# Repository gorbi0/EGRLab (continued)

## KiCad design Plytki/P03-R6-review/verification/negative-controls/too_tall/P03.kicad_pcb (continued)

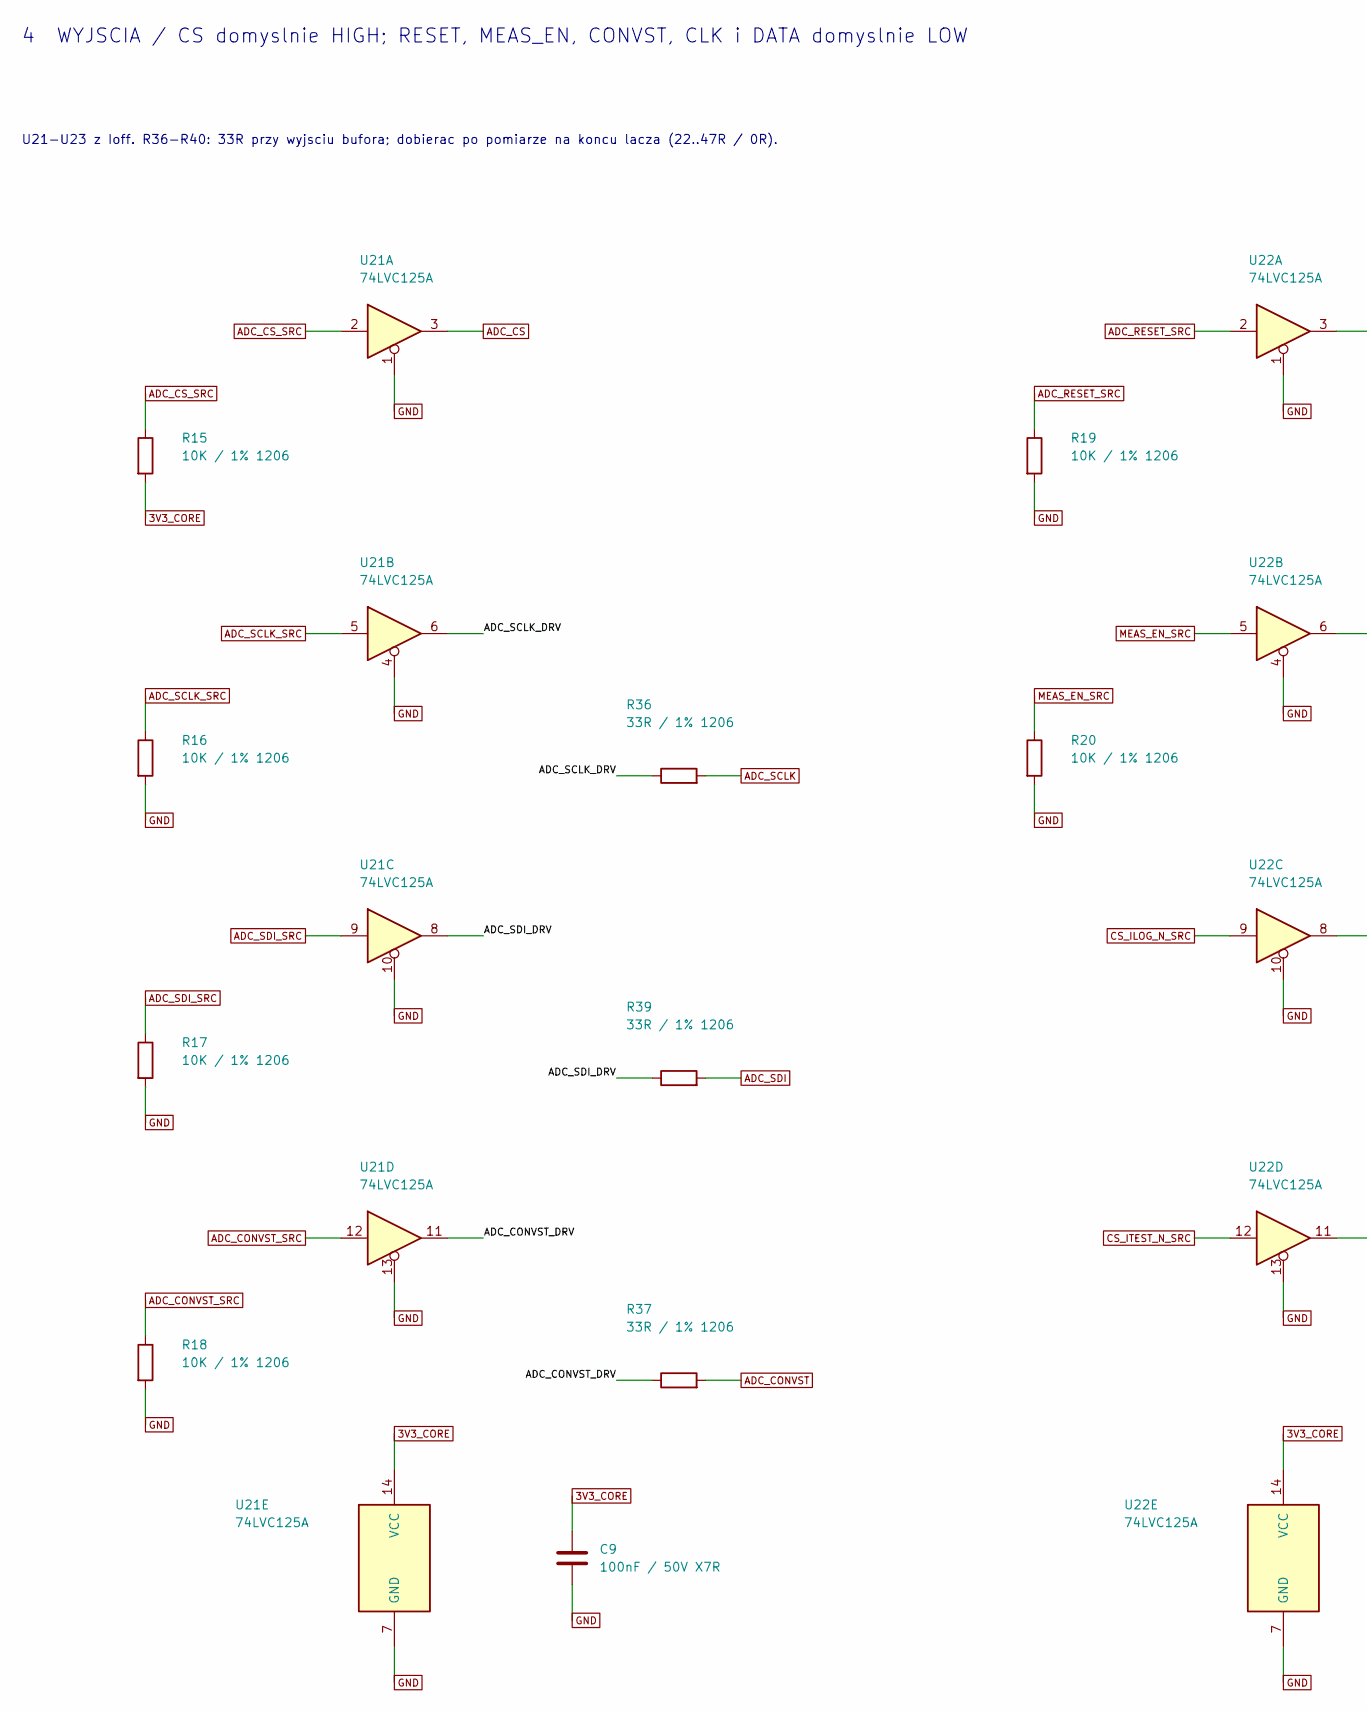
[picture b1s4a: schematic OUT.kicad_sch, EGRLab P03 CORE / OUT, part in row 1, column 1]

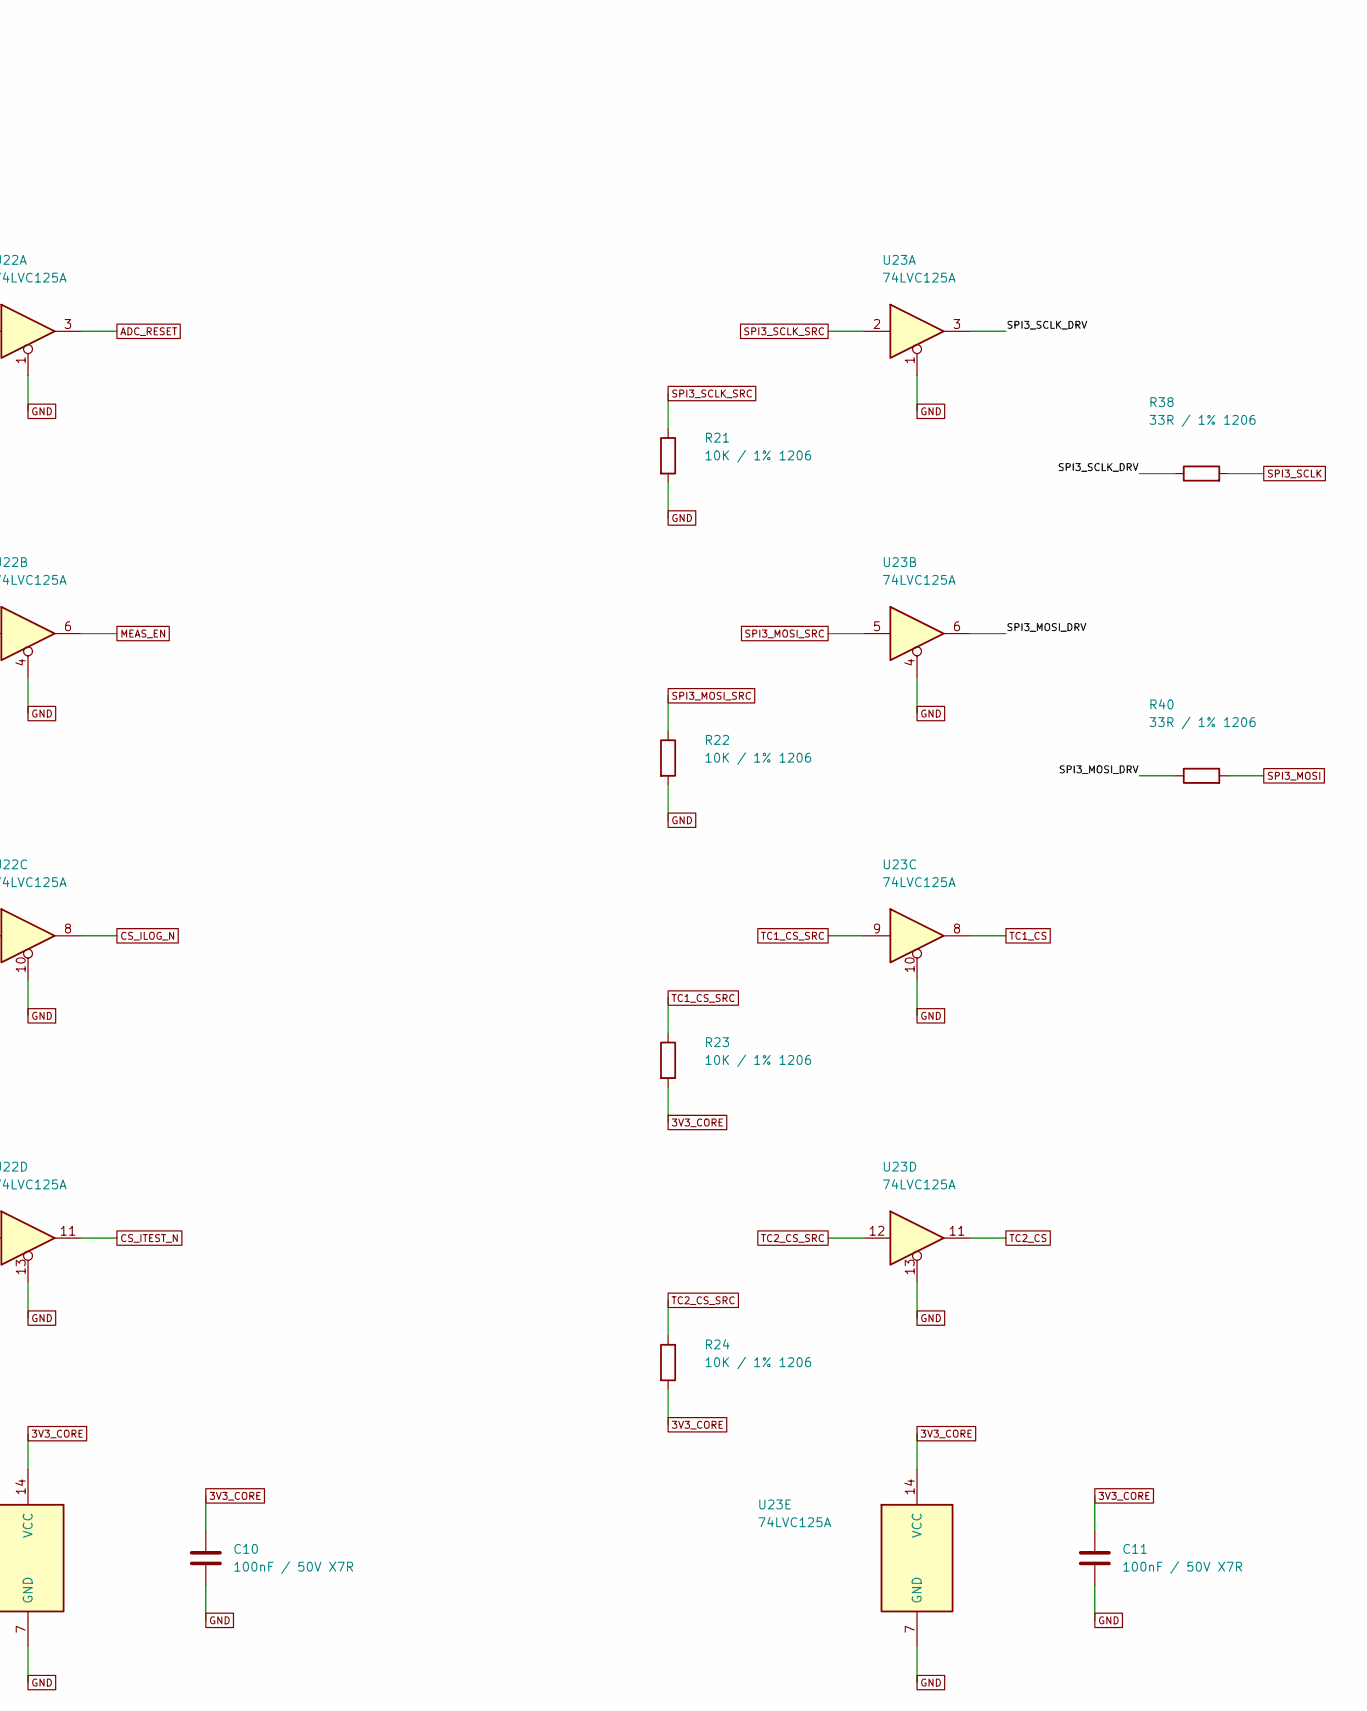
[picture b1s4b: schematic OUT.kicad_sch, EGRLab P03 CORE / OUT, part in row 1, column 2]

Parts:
C9, C10, C11: 100nF / 50V X7R; C_1206_3216Metric_Pad1.33x1.80mm_HandSolder; MPN GRM31CR71H104KA01L
R15, R16, R17, R18, R19, R20, R21, R22, R23, R24: 10K / 1% 1206; R_1206_3216Metric_Pad1.30x1.75mm_HandSolder; MPN RC1206FR-0710KL
R36, R37, R38, R39, R40: 33R / 1% 1206; R_1206_3216Metric_Pad1.30x1.75mm_HandSolder; MPN RC1206FR-0733RL
U21, U22, U23: 74LVC125A; SOIC-14_3.9x8.7mm_P1.27mm; MPN 74LVC125AD,118 (Nexperia)

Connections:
/OUT/ADC_CONVST_DRV: R37.1, U21.11
/OUT/ADC_SCLK_DRV: R36.1, U21.6
/OUT/ADC_SDI_DRV: R39.1, U21.8
/OUT/SPI3_MOSI_DRV: R40.1, U23.6
/OUT/SPI3_SCLK_DRV: R38.1, U23.3
ADC_CONVST: R37.2; also elsewhere on the board
ADC_CONVST_SRC: R18.1, U21.12; also elsewhere on the board
ADC_CS: U21.3; also elsewhere on the board
ADC_CS_SRC: R15.1, U21.2; also elsewhere on the board
ADC_RESET: U22.3; also elsewhere on the board
ADC_RESET_SRC: R19.1, U22.2; also elsewhere on the board
ADC_SCLK: R36.2; also elsewhere on the board
ADC_SCLK_SRC: R16.1, U21.5; also elsewhere on the board
ADC_SDI: R39.2; also elsewhere on the board
ADC_SDI_SRC: R17.1, U21.9; also elsewhere on the board
CS_ILOG_N_SRC: U22.9; also elsewhere on the board
CS_ITEST_N: U22.11; also elsewhere on the board
CS_ITEST_N_SRC: U22.12; also elsewhere on the board
GND: C9.2, C10.2, C11.2, R16.2, R17.2, R18.2, R19.2, R20.2, R21.2, R22.2, U21.1, U21.4, U21.7 (GND), U21.10, U21.13, U22.1, U22.4, U22.7 (GND), U22.10, U22.13, U23.1, U23.4, U23.7 (GND), U23.10, U23.13; also elsewhere on the board
MEAS_EN: U22.6; also elsewhere on the board
MEAS_EN_SRC: R20.1, U22.5; also elsewhere on the board
SPI3_MOSI: R40.2; also elsewhere on the board
SPI3_MOSI_SRC: R22.1, U23.5; also elsewhere on the board
SPI3_SCLK: R38.2; also elsewhere on the board
SPI3_SCLK_SRC: R21.1, U23.2; also elsewhere on the board
TC1_CS: U23.8; also elsewhere on the board
TC1_CS_SRC: R23.1, U23.9; also elsewhere on the board
TC2_CS: U23.11; also elsewhere on the board
TC2_CS_SRC: R24.1, U23.12; also elsewhere on the board

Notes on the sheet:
4 WYJSCIA / CS domyslnie HIGH; RESET, MEAS_EN, CONVST, CLK i DATA domyslnie LOW
U21-U23 z Ioff. R36-R40: 33R przy wyjsciu bufora; dobierac po pomiarze na koncu lacza (22..47R / 0R).

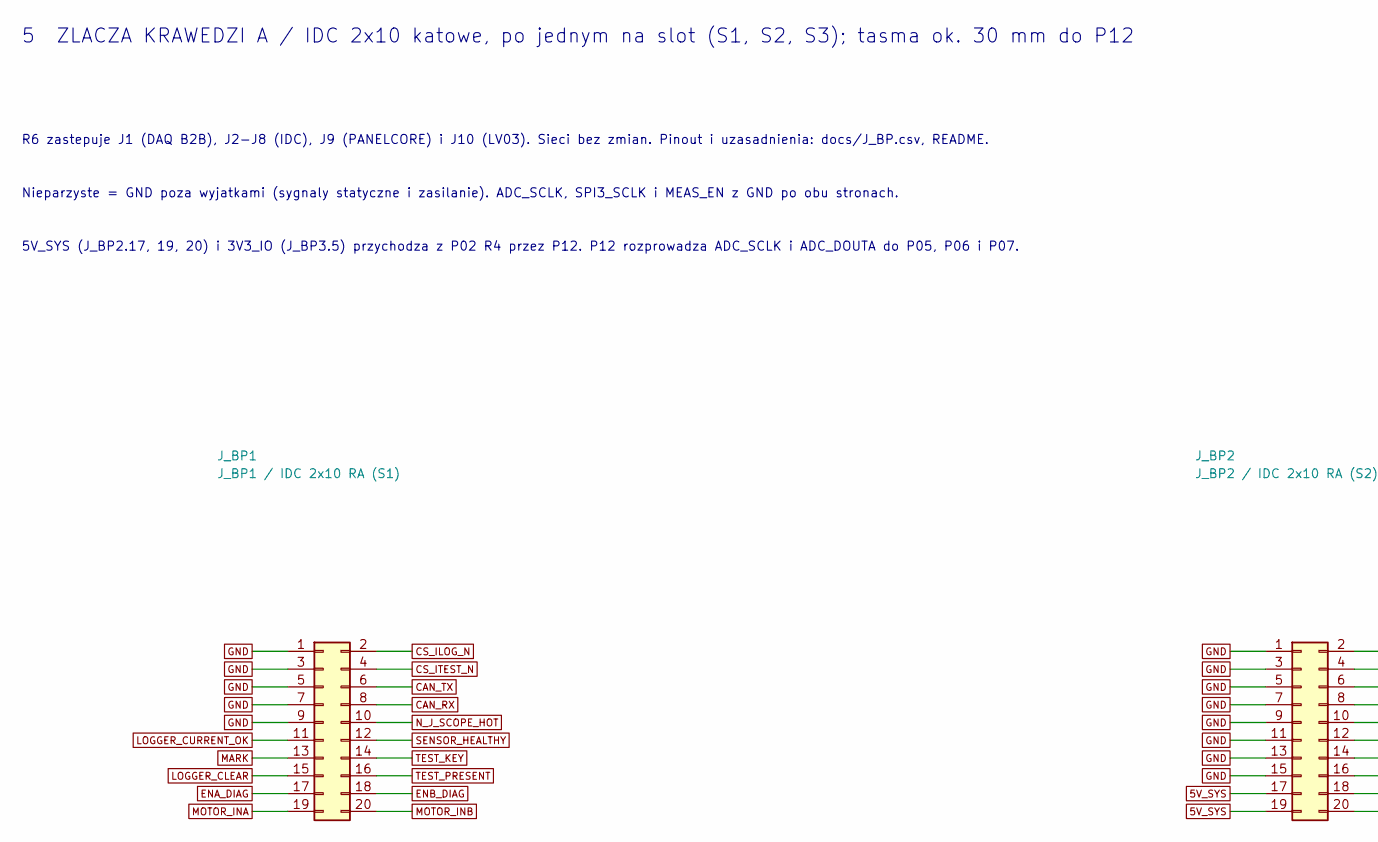
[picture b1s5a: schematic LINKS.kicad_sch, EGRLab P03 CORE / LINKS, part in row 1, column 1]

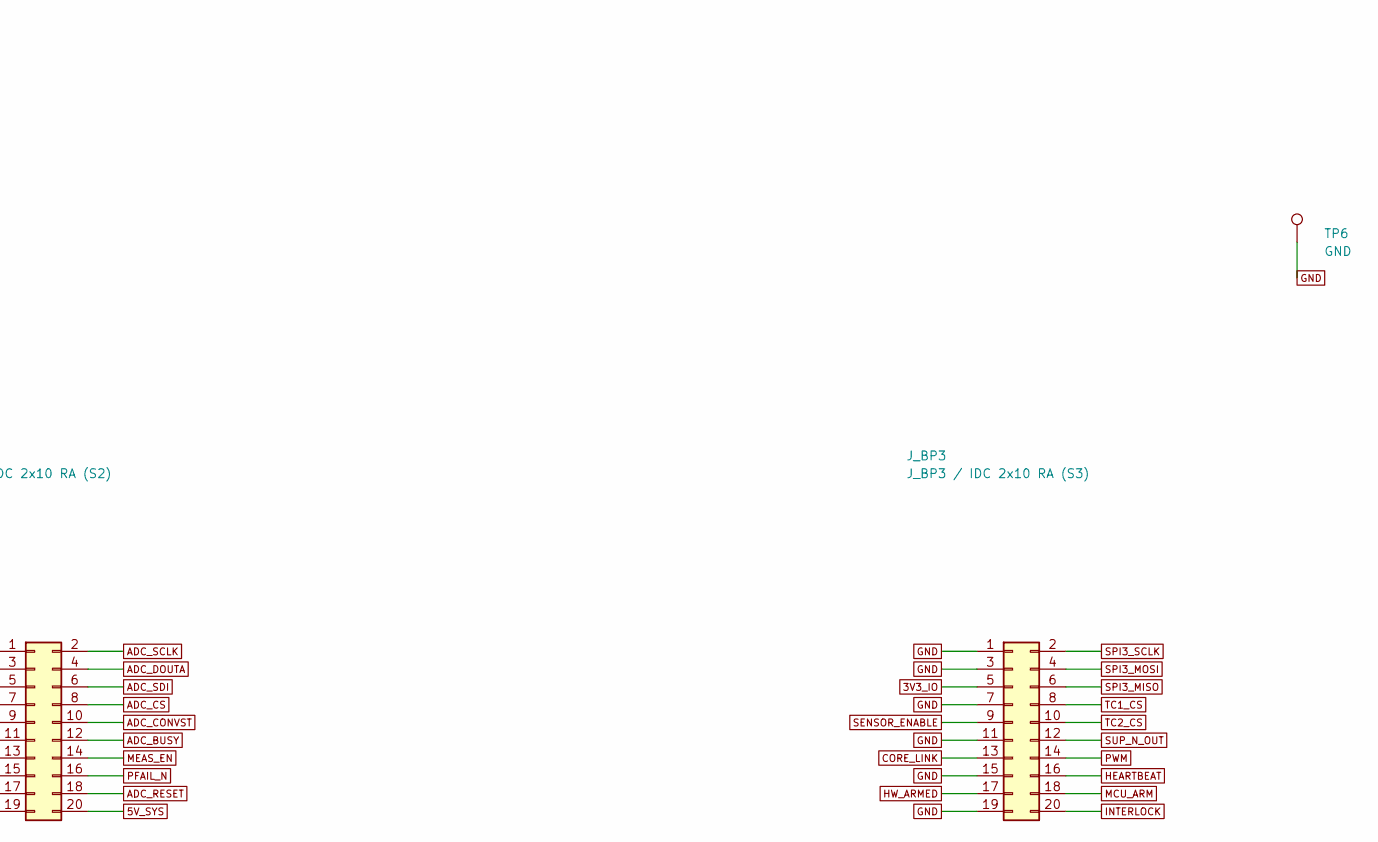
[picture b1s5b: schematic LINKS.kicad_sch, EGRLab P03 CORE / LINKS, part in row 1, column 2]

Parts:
J_BP1: J_BP1 / IDC 2x10 RA (S1); IDC-Header_2x10_P2.54mm_Horizontal; MPN IDC box header 2x10, 2.54 mm, right ang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
J_BP2: J_BP2 / IDC 2x10 RA (S2); IDC-Header_2x10_P2.54mm_Horizontal; MPN IDC box header 2x10, 2.54 mm, right ang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
J_BP3: J_BP3 / IDC 2x10 RA (S3); IDC-Header_2x10_P2.54mm_Horizontal; MPN IDC box header 2x10, 2.54 mm, right ang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
TP6: GND; TestPad_1; MPN PCB test pad

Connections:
3V3_IO: J_BP3.5; also elsewhere on the board
5V_SYS: J_BP2.17, J_BP2.19, J_BP2.20; also elsewhere on the board
ADC_BUSY: J_BP2.12; also elsewhere on the board
ADC_CONVST: J_BP2.10; also elsewhere on the board
ADC_CS: J_BP2.8; also elsewhere on the board
ADC_DOUTA: J_BP2.4; also elsewhere on the board
ADC_RESET: J_BP2.18; also elsewhere on the board
ADC_SCLK: J_BP2.2; also elsewhere on the board
ADC_SDI: J_BP2.6; also elsewhere on the board
CAN_RX: J_BP1.8; also elsewhere on the board
CAN_TX: J_BP1.6; also elsewhere on the board
CORE_LINK: J_BP3.13; also elsewhere on the board
CS_ITEST_N: J_BP1.4; also elsewhere on the board
ENA_DIAG: J_BP1.17; also elsewhere on the board
ENB_DIAG: J_BP1.18; also elsewhere on the board
GND: J_BP1.1, J_BP1.3, J_BP1.5, J_BP1.7, J_BP1.9, J_BP2.1, J_BP2.3, J_BP2.5, J_BP2.7, J_BP2.9, J_BP2.11, J_BP2.13, J_BP2.15, J_BP3.1, J_BP3.3, J_BP3.7, J_BP3.11, J_BP3.15, J_BP3.19, TP6.1; also elsewhere on the board
HEARTBEAT: J_BP3.16; also elsewhere on the board
HW_ARMED: J_BP3.17; also elsewhere on the board
INTERLOCK: J_BP3.20; also elsewhere on the board
LOGGER_CLEAR: J_BP1.15; also elsewhere on the board
MARK: J_BP1.13; also elsewhere on the board
MCU_ARM: J_BP3.18; also elsewhere on the board
MEAS_EN: J_BP2.14; also elsewhere on the board
MOTOR_INA: J_BP1.19; also elsewhere on the board
MOTOR_INB: J_BP1.20; also elsewhere on the board
N_J_SCOPE_HOT: J_BP1.10; also elsewhere on the board
PWM: J_BP3.14; also elsewhere on the board
SENSOR_ENABLE: J_BP3.9; also elsewhere on the board
SENSOR_HEALTHY: J_BP1.12; also elsewhere on the board
SPI3_MISO: J_BP3.6; also elsewhere on the board
SPI3_MOSI: J_BP3.4; also elsewhere on the board
SPI3_SCLK: J_BP3.2; also elsewhere on the board
SUP_N_OUT: J_BP3.12; also elsewhere on the board
TC1_CS: J_BP3.8; also elsewhere on the board
TC2_CS: J_BP3.10; also elsewhere on the board
TEST_KEY: J_BP1.14; also elsewhere on the board
TEST_PRESENT: J_BP1.16; also elsewhere on the board

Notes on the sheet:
5 ZLACZA KRAWEDZI A / IDC 2x10 katowe, po jednym na slot (S1, S2, S3); tasma ok. 30 mm do P12
R6 zastepuje J1 (DAQ B2B), J2-J8 (IDC), J9 (PANELCORE) i J10 (LV03). Sieci bez zmian. Pinout i uzasadnienia: docs/J_BP.csv, README.
Nieparzyste = GND poza wyjatkami (sygnaly statyczne i zasilanie). ADC_SCLK, SPI3_SCLK i MEAS_EN z GND po obu stronach.
5V_SYS (J_BP2.17, 19, 20) i 3V3_IO (J_BP3.5) przychodza z P02 R4 przez P12. P12 rozprowadza ADC_SCLK i ADC_DOUTA do P05, P06 i P07.

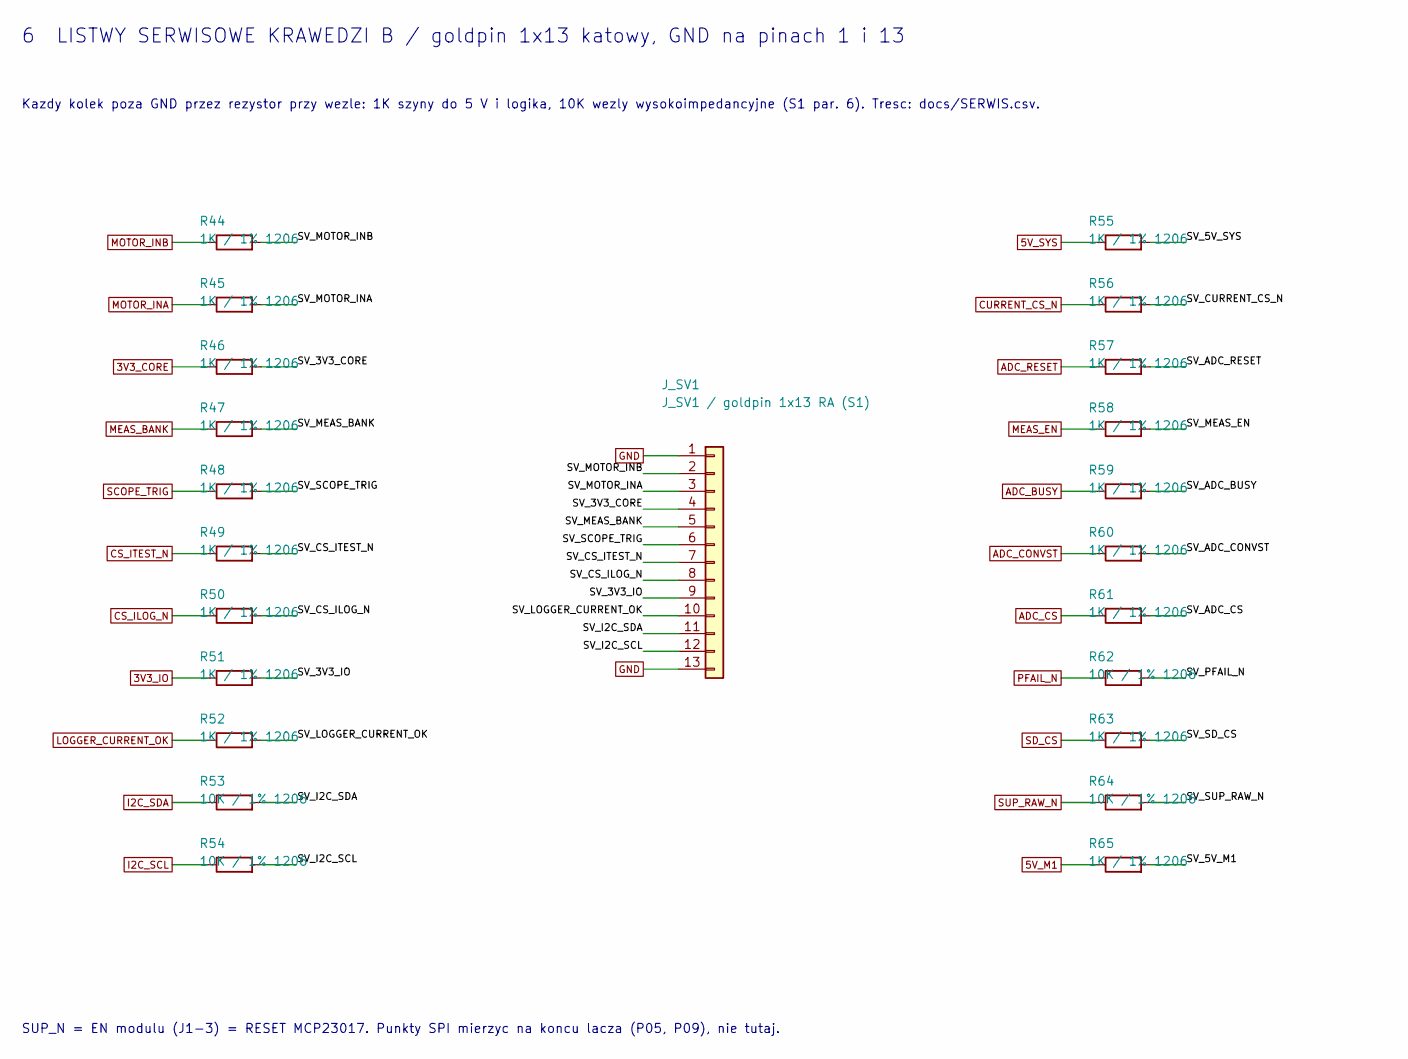
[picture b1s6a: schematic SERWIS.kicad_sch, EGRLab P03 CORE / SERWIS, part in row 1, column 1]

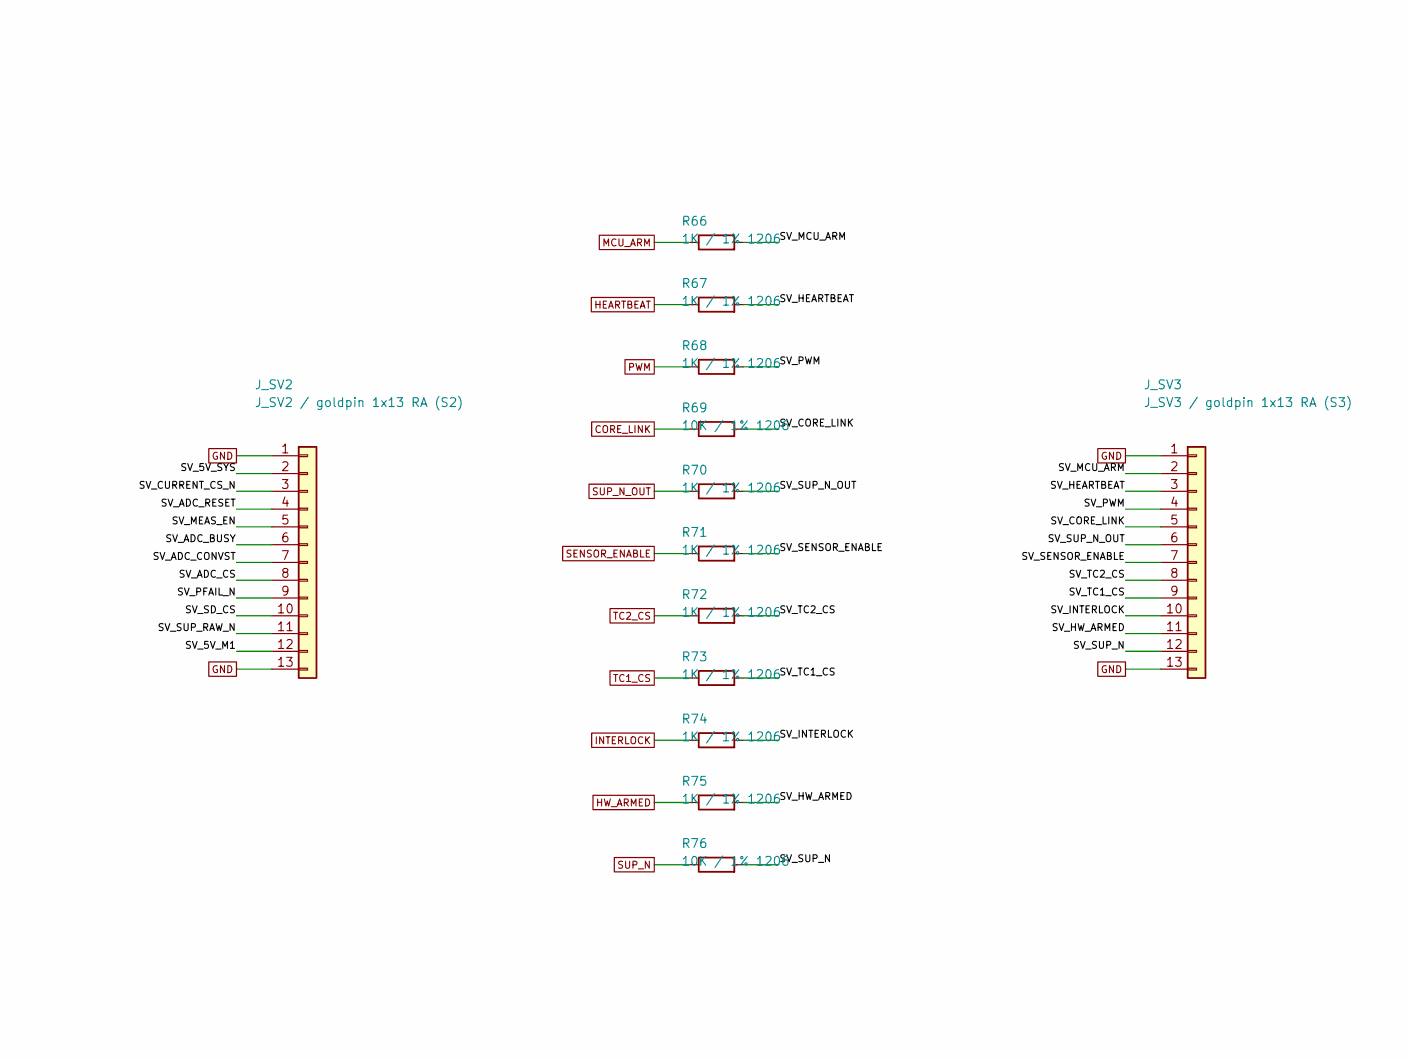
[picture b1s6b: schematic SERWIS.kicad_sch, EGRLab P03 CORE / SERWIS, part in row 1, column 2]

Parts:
J_SV1: J_SV1 / goldpin 1x13 RA (S1); PinHeader_1x13_P2.54mm_Horizontal; MPN Pin header 1x13, 2.54 mm, right angle, 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
J_SV2: J_SV2 / goldpin 1x13 RA (S2); PinHeader_1x13_P2.54mm_Horizontal; MPN Pin header 1x13, 2.54 mm, right angle, 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
J_SV3: J_SV3 / goldpin 1x13 RA (S3); PinHeader_1x13_P2.54mm_Horizontal; MPN Pin header 1x13, 2.54 mm, right angle, 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
R44, R45, R46, R47, R48, R49, R50, R51, R52, R55, R56, R57, R58, R59, R60, R61, R63, R65, R66, R67, R68, R70, R71, R72, R73, R74, R75: 1K / 1% 1206; R_1206_3216Metric_Pad1.30x1.75mm_HandSolder; MPN RC1206FR-071KL
R53, R54, R62, R64, R69, R76: 10K / 1% 1206; R_1206_3216Metric_Pad1.30x1.75mm_HandSolder; MPN RC1206FR-0710KL

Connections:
3V3_IO: R51.1; also elsewhere on the board
5V_M1: R65.1; also elsewhere on the board
5V_SYS: R55.1; also elsewhere on the board
/SERWIS/SV_3V3_CORE: J_SV1.10, R52.2
/SERWIS/SV_3V3_IO: J_SV1.9, R51.2
/SERWIS/SV_5V_M1: J_SV2.12, R65.2
/SERWIS/SV_5V_SYS: J_SV2.2, R55.2
/SERWIS/SV_ADC_BUSY: J_SV2.6, R59.2
/SERWIS/SV_ADC_CONVST: J_SV2.7, R60.2
/SERWIS/SV_ADC_CS: J_SV2.8, R61.2
/SERWIS/SV_ADC_RESET: J_SV2.4, R57.2
/SERWIS/SV_CORE_LINK: J_SV3.5, R69.2
/SERWIS/SV_CS_ILOG_N: J_SV1.5, R47.2
/SERWIS/SV_CS_ITEST_N: J_SV1.7, R49.2
/SERWIS/SV_CURRENT_CS_N: J_SV2.9, R62.2
/SERWIS/SV_HEARTBEAT: J_SV3.3, R67.2
/SERWIS/SV_HW_ARMED: J_SV3.11, R75.2
/SERWIS/SV_I2C_SCL: J_SV1.8, R50.2
/SERWIS/SV_I2C_SDA: J_SV1.11, R53.2
/SERWIS/SV_INTERLOCK: J_SV3.10, R74.2
/SERWIS/SV_LOGGER_CURRENT_OK: J_SV1.12, R54.2
/SERWIS/SV_MCU_ARM: J_SV3.2, R66.2
/SERWIS/SV_MEAS_BANK: J_SV1.4, R46.2
/SERWIS/SV_MEAS_EN: J_SV2.5, R58.2
/SERWIS/SV_MOTOR_INA: J_SV1.3, R45.2
/SERWIS/SV_MOTOR_INB: J_SV1.2, R44.2
/SERWIS/SV_PFAIL_N: J_SV2.3, R56.2
/SERWIS/SV_PWM: J_SV3.4, R68.2
/SERWIS/SV_SCOPE_TRIG: J_SV1.6, R48.2
/SERWIS/SV_SD_CS: J_SV2.10, R63.2
/SERWIS/SV_SENSOR_ENABLE: J_SV3.7, R71.2
/SERWIS/SV_SUP_N: J_SV3.12, R76.2
/SERWIS/SV_SUP_N_OUT: J_SV3.6, R70.2
/SERWIS/SV_SUP_RAW_N: J_SV2.11, R64.2
/SERWIS/SV_TC1_CS: J_SV3.9, R73.2
/SERWIS/SV_TC2_CS: J_SV3.8, R72.2
ADC_BUSY: R59.1; also elsewhere on the board
ADC_CONVST: R60.1; also elsewhere on the board
ADC_CS: R61.1; also elsewhere on the board
ADC_RESET: R57.1; also elsewhere on the board
CORE_LINK: R69.1; also elsewhere on the board
CS_ITEST_N: R49.1; also elsewhere on the board
GND: J_SV1.1, J_SV1.13, J_SV2.1, J_SV2.13, J_SV3.1, J_SV3.13; also elsewhere on the board
HEARTBEAT: R67.1; also elsewhere on the board
HW_ARMED: R75.1; also elsewhere on the board
I2C_SDA: R53.1; also elsewhere on the board
INTERLOCK: R74.1; also elsewhere on the board
MCU_ARM: R66.1; also elsewhere on the board
MEAS_EN: R58.1; also elsewhere on the board
MOTOR_INA: R45.1; also elsewhere on the board
MOTOR_INB: R44.1; also elsewhere on the board
PWM: R68.1; also elsewhere on the board
SCOPE_TRIG: R48.1; also elsewhere on the board
SD_CS: R63.1; also elsewhere on the board
SENSOR_ENABLE: R71.1; also elsewhere on the board
SUP_N: R76.1; also elsewhere on the board
SUP_N_OUT: R70.1; also elsewhere on the board
SUP_RAW_N: R64.1; also elsewhere on the board
TC1_CS: R73.1; also elsewhere on the board
TC2_CS: R72.1; also elsewhere on the board

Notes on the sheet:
6 LISTWY SERWISOWE KRAWEDZI B / goldpin 1x13 katowy, GND na pinach 1 i 13
Kazdy kolek poza GND przez rezystor przy wezle: 1K szyny do 5 V i logika, 10K wezly wysokoimpedancyjne (S1 par. 6). Tresc: docs/SERWIS.csv.
SUP_N = EN modulu (J1-3) = RESET MCP23017. Punkty SPI mierzyc na koncu lacza (P05, P09), nie tutaj.

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
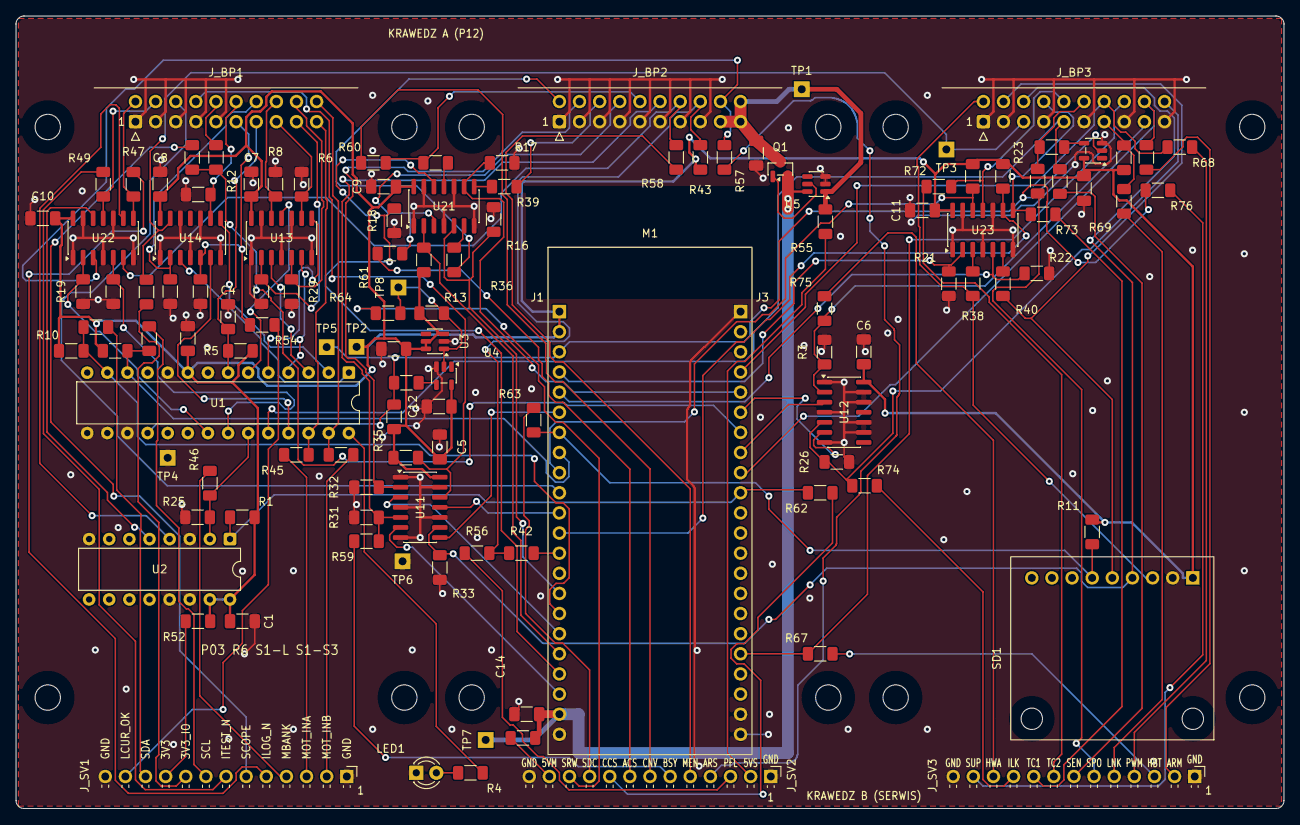
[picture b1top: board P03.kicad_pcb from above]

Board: 2 copper layers, 160.0 x 100.0 mm, 134 parts (0 on the bottom side), 119 nets.

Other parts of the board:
H1, H2, H3, H4, H5, H6, H7, H8, H9, H10, H11, H12: M3 NPTH

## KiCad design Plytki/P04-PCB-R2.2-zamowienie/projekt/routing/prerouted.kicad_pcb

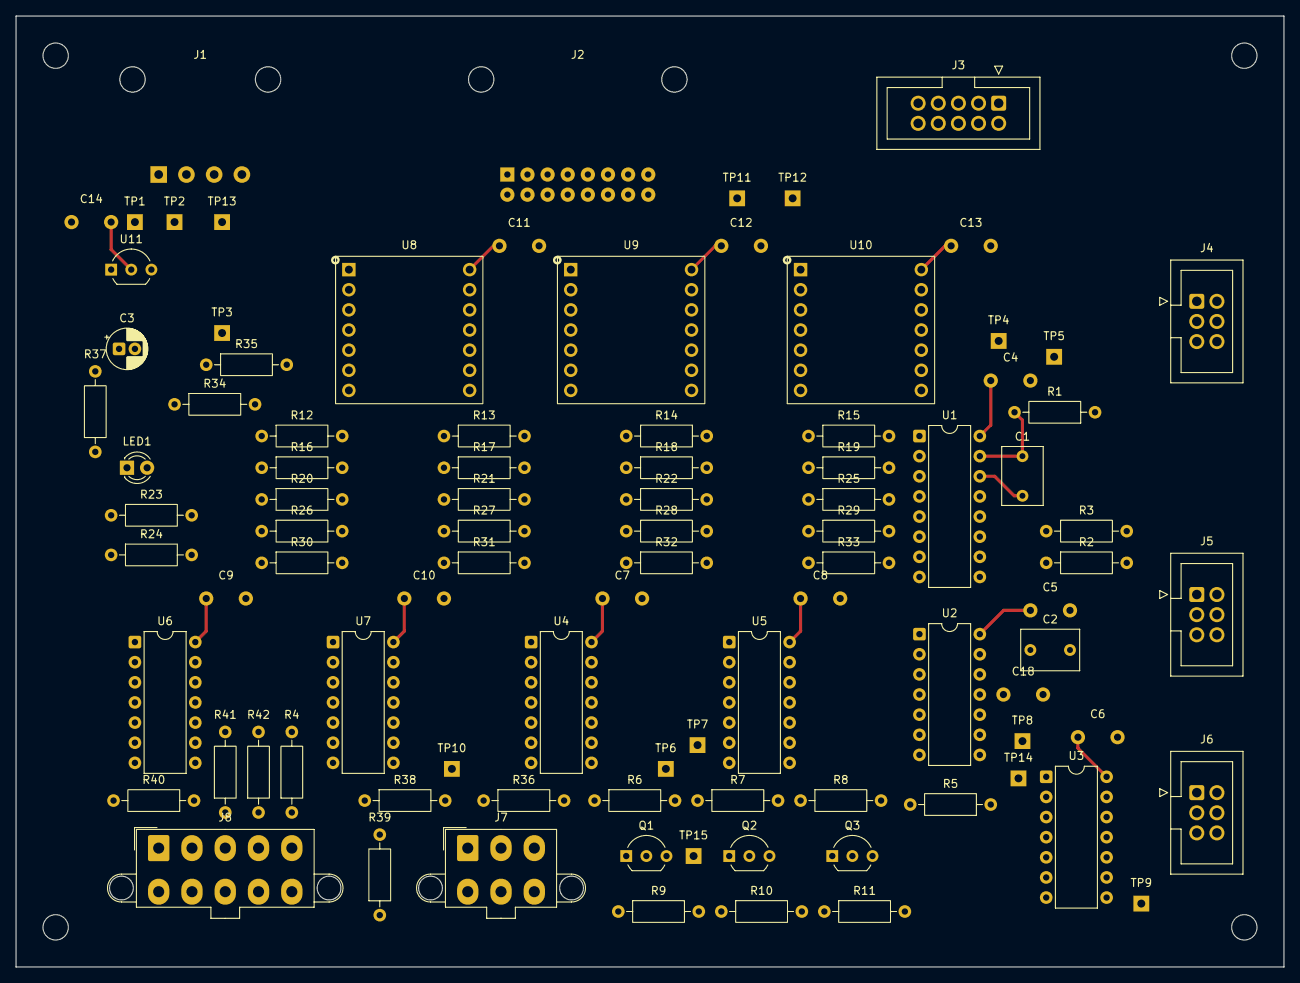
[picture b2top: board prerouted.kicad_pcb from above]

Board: 2 copper layers, 160.0 x 120.0 mm, 99 parts (0 on the bottom side), 67 nets.

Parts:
C1, C2: 1u; C_Rect_L7.2mm_W5.0mm_P5.00mm
C3: 10u; CP_Radial_D5.0mm_P2.00mm
C4, C5, C6, C7, C8, C9, C10, C11, C12, C13, C14: 100n; C_Vishay_K15_H5_P5
C18: 1n; C_Vishay_K15_H5_P5
H1, H2, H3, H4: M3 NPTH
J1: LV04; PTH_LV04_4p_AWG22
J2: SAFE; PTH_SAFE_16p_AWG28
J3: DRIVE; IDC_10p_Wurth_Drill1.2
J4: SENSOR; IDC_6p_Wurth_Drill1.2
J5: DAQOK; IDC_6p_Wurth_Drill1.2
J6: PSUOK; IDC_6p_Wurth_Drill1.2
J7: PG; Molex_Mini-Fit_Jr_5566-06A2_2x03_P4.20mm_Vertical
J8: PANELSAFE; Molex_Mini-Fit_Jr_5566-10A2_2x05_P4.20mm_Vertical
LED1: POWER; LED_D3.0mm
Q1, Q2, Q3: 2N3904; TO-92_Inline_Wide
R1: 220K; R_Axial_DIN0207_L6.3mm_D2.5mm_P10.16mm_Horizontal
R2, R4, R6, R7, R8, R12, R13, R14, R15, R16, R17, R18, R19, R20, R21, R22, R23, R24, R25, R29, R31, R32, R33, R34, R35, R36: 10K; R_Axial_DIN0207_L6.3mm_D2.5mm_P10.16mm_Horizontal
R3, R37, R38, R39, R41, R42: 1K; R_Axial_DIN0207_L6.3mm_D2.5mm_P10.16mm_Horizontal
R5, R9, R10, R11, R28, R30: 100K; R_Axial_DIN0207_L6.3mm_D2.5mm_P10.16mm_Horizontal
R26, R27: 47K; R_Axial_DIN0207_L6.3mm_D2.5mm_P10.16mm_Horizontal
R40: 100R; R_Axial_DIN0207_L6.3mm_D2.5mm_P10.16mm_Horizontal
TP1: 3V3_IO; TestPad_1
TP2: GND; TestPad_1
TP3: LOCAL_SUP_N; TestPad_1
TP4: SUP_OK; TestPad_1
TP5: WD_Q; TestPad_1
TP6: SAFE_N; TestPad_1
TP7: SAFE_OK; TestPad_1
TP8: ARM_CLK; TestPad_1
TP9: HW_ARMED; TestPad_1
TP10: INTERLOCK; TestPad_1
TP11: MOTOR_PERMIT; TestPad_1
TP12: SENSOR_PERMIT; TestPad_1
TP13: 5V_SYS; TestPad_1
TP14: SAFE_WD; TestPad_1
TP15: Q1_B; TestPad_1
U1: CD74HC123E; DIP-16_W7.62mm
U2: SN74HC14N; DIP-14_W7.62mm
U3: SN74HC74N; DIP-14_W7.62mm
U4, U5, U6, U7: SN74HC08N; DIP-14_W7.62mm
U8, U9, U10: 74LVC125AD; Adapter_SO14_DIP14_W15.24_Kamami575068
U11: MCP100-300DI/TO; TO-92_Inline_Wide

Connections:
3V3_IO: C3.1, C4.1, C5.1, C6.1, C7.1, C8.1, C9.1, C10.1, C11.1, C12.1, C13.1, C14.1, J1.3, R1.1, R2.1, R37.1, R38.1, R39.1, R40.1, TP1.1, U1.16, U2.14, U3.2, U3.4, U3.10, U3.14, U4.14, U5.14, U6.14, U7.14, U8.14, U9.14, U10.13, U10.14, U11.2
5V_SYS: J1.1, TP13.1
/CON/PANEL_3V3: J8.1, R40.2
/CON/PG_3V3: J7.1, R39.2
/CON/PG_SEND: J7.4, R38.2
/ILK/MECH_KEY: U7.5, U7.8
/ILK/MECH_OK_P04: R24.1, R42.2, U7.9
/ILK/MODULES_OK: U7.3, U7.4
/ILK/OK_A: U6.3, U6.12
/ILK/OK_AB: U6.11, U7.1
/ILK/OK_B: U6.6, U6.13
/ILK/OK_C: U6.8, U7.2
/LED_PWR: LED1.2, R37.2
/OUT/ARM_BOTH: U4.3, U4.4
/OUT/MOTOR_REQ: U4.6, U5.12
/OUT/SENSOR_INTERLOCK: U5.3, U5.4
/OUT/SENSOR_KEY: U4.11, U5.1
/WD/ARM_BUTTON_N: C2.1, R2.2, R3.1, U2.3
/WD/ILK_BAD: R8.1, U2.8
/WD/Q1_B: Q1.2, R6.2, R9.1, TP15.1
/WD/Q2_B: Q2.2, R7.2, R10.1
/WD/Q3_B: Q3.2, R8.2, R11.1
/WD/SAFE_OK: TP7.1, U2.12, U7.12
/WD/SAFE_OK_N: U2.10, U2.13
/WD/SUP_BAD: R7.1, U2.6
/WD/SUP_OK: TP4.1, U1.3, U2.5, U5.8
/WD/WD_BAD: R6.1, U2.2
/WD/WD_C: C1.2, U1.14
/WD/WD_Q: TP5.1, U1.13, U2.1, U7.13
/WD/WD_RC: C1.1, R1.2, U1.15
ARM_CLK: J3.5, TP8.1, U2.4, U3.3
ARM_CONTACT: J8.9, R3.2
CORE_LINK: J2.13, R16.1, U9.2
CORE_LINK_P04: R29.1, U6.9, U9.3
DAQ_OK: J5.1, R19.1, U9.12
DAQ_OK_P04: R32.1, U6.2, U9.11
DRIVE_OK: J3.7, R20.1, U10.2
DRIVE_OK_P04: R33.1, U6.4, U10.3
GND: C2.2, C3.2, C4.2, C5.2, C6.2, C7.2, C8.2, C9.2, C10.2, C11.2, C12.2, C13.2, C14.2, C18.2, J1.2, J1.4, J2.2, J2.6, J2.8, J2.10, J2.12, J2.14, J2.16, J3.4, J3.6, J3.8, J3.10, J4.4, J5.2, J6.2, J7.3, J7.6, J8.2, J8.10, LED1.1, Q1.1, Q2.1, Q3.1, R5.2, R9.2, R10.2, R11.2, R12.2, R13.2, R14.2, R15.2, R16.2, R17.2, R18.2, R19.2, R20.2, R21.2, R22.2, R23.2, R24.2, R25.2, R26.2, R27.2, R28.2, R29.2, R30.2, R31.2, R32.2, R33.2, R34.2, R35.2, R36.2, TP2.1, U1.1, U1.8, U1.9, U1.10, U1.11, U2.7, U3.7, U3.11, U3.12, U3.13, U4.7, U5.7, U6.7, U7.7, U8.1, U8.4, U8.7, U8.10, U8.13, U9.1, U9.4, U9.7, U9.10, U9.13, U10.1, U10.4, U10.7, U10.10, U10.12, U11.3
HEARTBEAT: J2.3, R13.1, U8.5
HEARTBEAT_P04: R26.1, U1.2, U8.6
HW_ARMED: J2.7, TP9.1, U3.5, U4.1
INTERLOCK: J2.9, R36.1, TP10.1, U2.9, U4.5, U5.2, U7.6
LOCAL_SUP_N: TP3.1, U5.10, U11.1
MCU_ARM: J2.5, R14.1, U8.9
MCU_ARM_P04: R27.1, U4.2, U8.8
MECH_OK: J8.4, R42.1
MOTOR_PERMIT: J3.1, TP11.1, U4.10, U5.11
PG_LINK: J7.5, R22.1, U10.9
PG_LINK_P04: R35.1, U6.10, U10.8
PSU_OK: J6.1, R18.1, U9.9
PSU_OK_P04: R31.1, U6.1, U9.8
PWM: J2.1, R12.1, U8.2
PWM_OUT: J3.3, U4.8
PWM_P04: R25.1, U4.9, U8.3
SAFE_N: C18.1, J3.9, J7.2, Q1.3, Q2.3, Q3.3, R4.2, R5.1, TP6.1, U2.11
SAFE_WD: TP14.1, U3.1, U5.5, U5.13, U7.11
SENSOR_ENABLE: J2.11, R15.1, U8.12
SENSOR_ENABLE_P04: R28.1, U4.12, U8.11
SENSOR_OK: J4.3, R21.1, U10.5
SENSOR_OK_P04: R34.1, U6.5, U10.6
SENSOR_PERMIT: J4.1, TP12.1, U5.6
STOP_NC_OUT: J8.7, R4.1
SUP_N: J2.15, R17.1, U9.5
SUP_N_P04: R30.1, U5.9, U9.6
TEST_KEY: J8.3, R41.1
TEST_KEY_P04: R23.1, R41.2, U4.13, U7.10
